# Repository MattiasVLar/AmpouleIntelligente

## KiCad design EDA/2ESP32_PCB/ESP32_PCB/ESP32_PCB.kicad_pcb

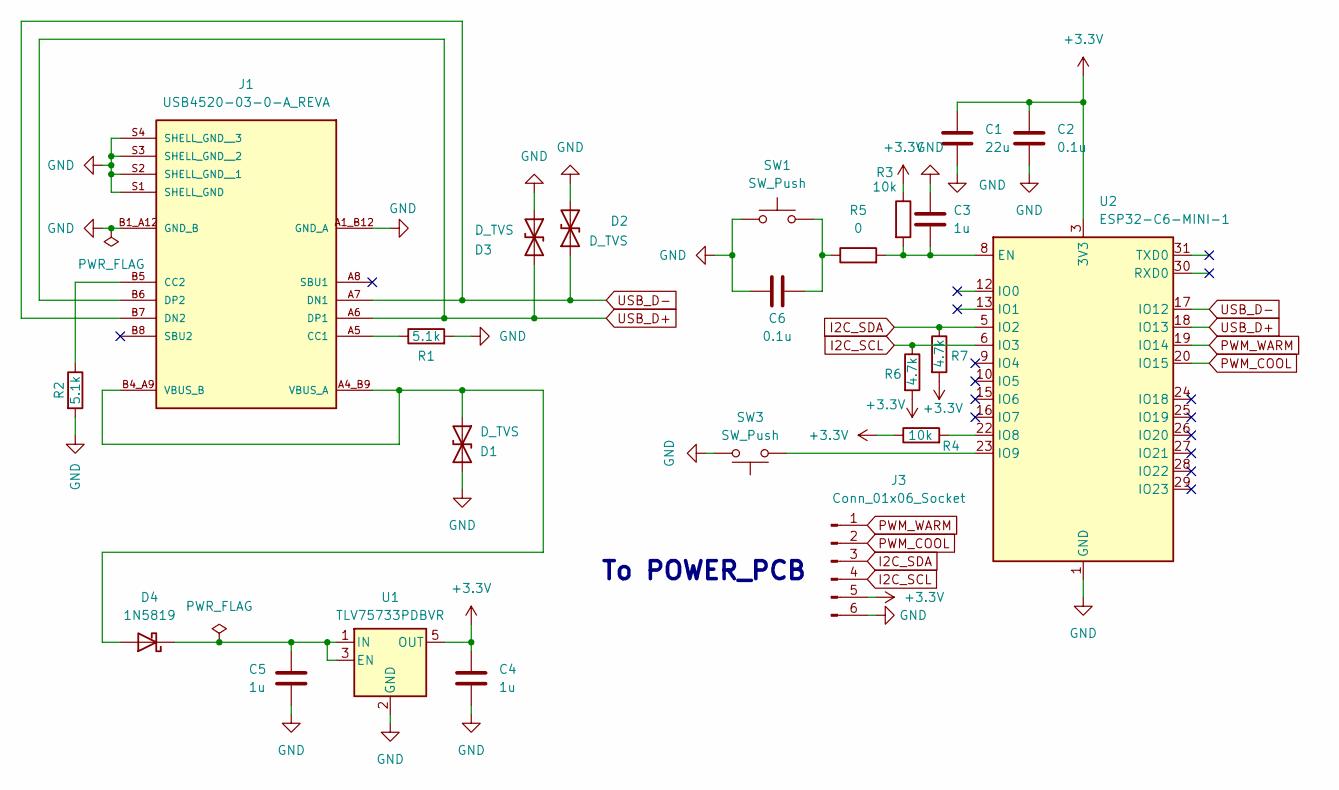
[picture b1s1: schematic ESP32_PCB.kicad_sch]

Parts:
C1: 22u; C_0603_1608Metric_Pad1.08x0.95mm_HandSolder; Digikey 1276-1274-1-ND
C2, C6: 0.1u; C_0603_1608Metric_Pad1.08x0.95mm_HandSolder; Digikey 311-1088-1-ND
C3, C4, C5: 1u; C_0603_1608Metric_Pad1.08x0.95mm_HandSolder; Digikey 445-CGA3E1X7R1C105K080DCCT-ND
D1: D_TVS; D_SOD-323F; Digikey 296-TSD05DYFRCT-ND
D2, D3: D_TVS; D_SOD-323F; Digikey 296-TSD05CDYFRCT-ND
D4: 1N5819; SDO_SOD123_DIO-L; Digikey B140HWDICT-ND
J1: USB4520-03-0-A_REVA; GCT_USB4520-03-0-A_REVA; PARTREV A
J3: Conn_01x06_Socket; EdgeConn
R1, R2: 5.1k; R_0603_1608Metric_Pad0.98x0.95mm_HandSolder; Digikey 311-5.10KHRCT-ND
R3, R4: 10k; R_0603_1608Metric_Pad0.98x0.95mm_HandSolder; Digikey 311-10.0KHRCT-ND
R5: 0; R_0603_1608Metric_Pad0.98x0.95mm_HandSolder; Digikey 311-0.0GRCT-ND
R6, R7: 4.7k; R_0603_1608Metric_Pad0.98x0.95mm_HandSolder; Digikey 311-4.70KHRCT-ND
SW1, SW3: SW_Push; SW_B3U-1000P; Digikey SW1020CT-ND
U1: TLV75733PDBVR; SOT-23-5; Digikey 296-50414-1-ND
U2: ESP32-C6-MINI-1; Digikey 1965-ESP32-C6-MINI-1-H4CT-ND

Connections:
+3.3V: C1.1, C2.2, C4.1, J3.5, R3.1, R4.1, R6.2, R7.2, U1.5 (OUT), U2.3 (3V3)
GND: C1.2, C2.1, C3.2, C4.2, C5.2, C6.2, D1.2 (A2), D2.2 (A2), D3.1 (A1), J1.A1_B12 (GND_A), J1.B1_A12 (GND_B), J1.S1 (SHELL_GND), J1.S2 (SHELL_GND__1), J1.S3 (SHELL_GND__2), J1.S4 (SHELL_GND__3), J3.6, R1.2, R2.2, SW1.1, SW3.2, U1.2 (GND), U2.1 (GND), U2.2 (GND), U2.11 (GND), U2.14 (GND), U2.36 (GND), U2.37 (GND), U2.38 (GND), U2.39 (GND), U2.40 (GND), U2.41 (GND), U2.42 (GND), U2.43 (GND), U2.44 (GND), U2.45 (GND), U2.46 (GND), U2.47 (GND), U2.48 (GND), U2.49 (GND), U2.50 (GND), U2.51 (GND), U2.52 (GND), U2.53 (GND)
I2C_SCL: J3.4, R6.1, U2.6 (IO3)
I2C_SDA: J3.3, R7.1, U2.5 (IO2)
unnamed: C6.1, R5.1, SW1.2
unnamed: D1.1 (A1), D4.2 (A), J1.A4_B9 (VBUS_A), J1.B4_A9 (VBUS_B)
unnamed: C5.1, D4.1 (K), U1.1 (IN), U1.3 (EN)
unnamed: J1.A5 (CC1), R1.1
unnamed: J1.B5 (CC2), R2.1
unnamed: C3.1, R3.2, R5.2, U2.8 (EN)
unnamed: R4.2, U2.22 (IO8)
unnamed: SW3.1, U2.23 (IO9)
PWM_COOL: J3.2, U2.20 (IO15)
PWM_WARM: J3.1, U2.19 (IO14)
USB_D+: D3.2 (A2), J1.A6 (DP1), J1.B6 (DP2), U2.18 (IO13)
USB_D-: D2.1 (A1), J1.A7 (DN1), J1.B7 (DN2), U2.17 (IO12)

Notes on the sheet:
To POWER_PCB

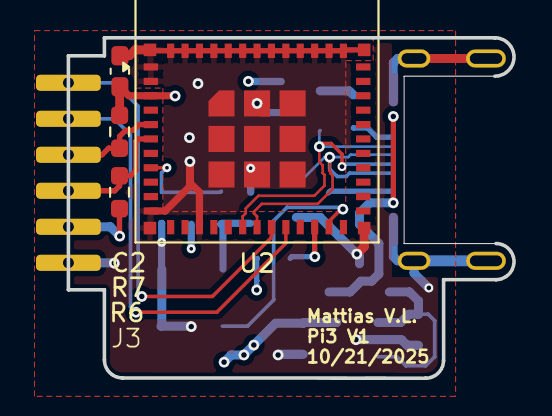
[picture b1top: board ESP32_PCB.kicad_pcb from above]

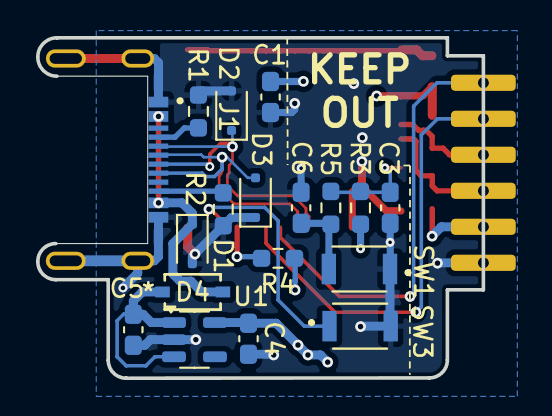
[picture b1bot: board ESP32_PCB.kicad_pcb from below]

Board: 4 copper layers, 24.8 x 18.9 mm, 23 parts (18 on the bottom side), 16 nets.

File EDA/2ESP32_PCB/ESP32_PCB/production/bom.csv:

Designator,Footprint,Quantity,Value,LCSC Part #
C1,0603,1,22u,
"C2, C6",0603,2,0.1u,
"C3, C4, C5",0603,3,1u,
"D1, D2, D3",D_SOD-323F,3,D_TVS,
D4,SDO_SOD123_DIO-L,1,1N5819,
J1,GCT_USB4520-03-0-A_REVA,1,USB4520-03-0-A_REVA,
J3,EdgeConn,1,Conn_01x06_Socket,
"R1, R2",0603,2,5.1k,
"R3, R4",0603,2,10k,
R5,0603,1,0,
"R6, R7",0603,2,4.7k,
"SW1, SW3",SW_B3U-1000P,2,SW_Push,
U1,SOT-23-5,1,TLV75533PDBV,
U2,ESP32-C6-MINI-1,1,ESP32-C6-MINI-1,

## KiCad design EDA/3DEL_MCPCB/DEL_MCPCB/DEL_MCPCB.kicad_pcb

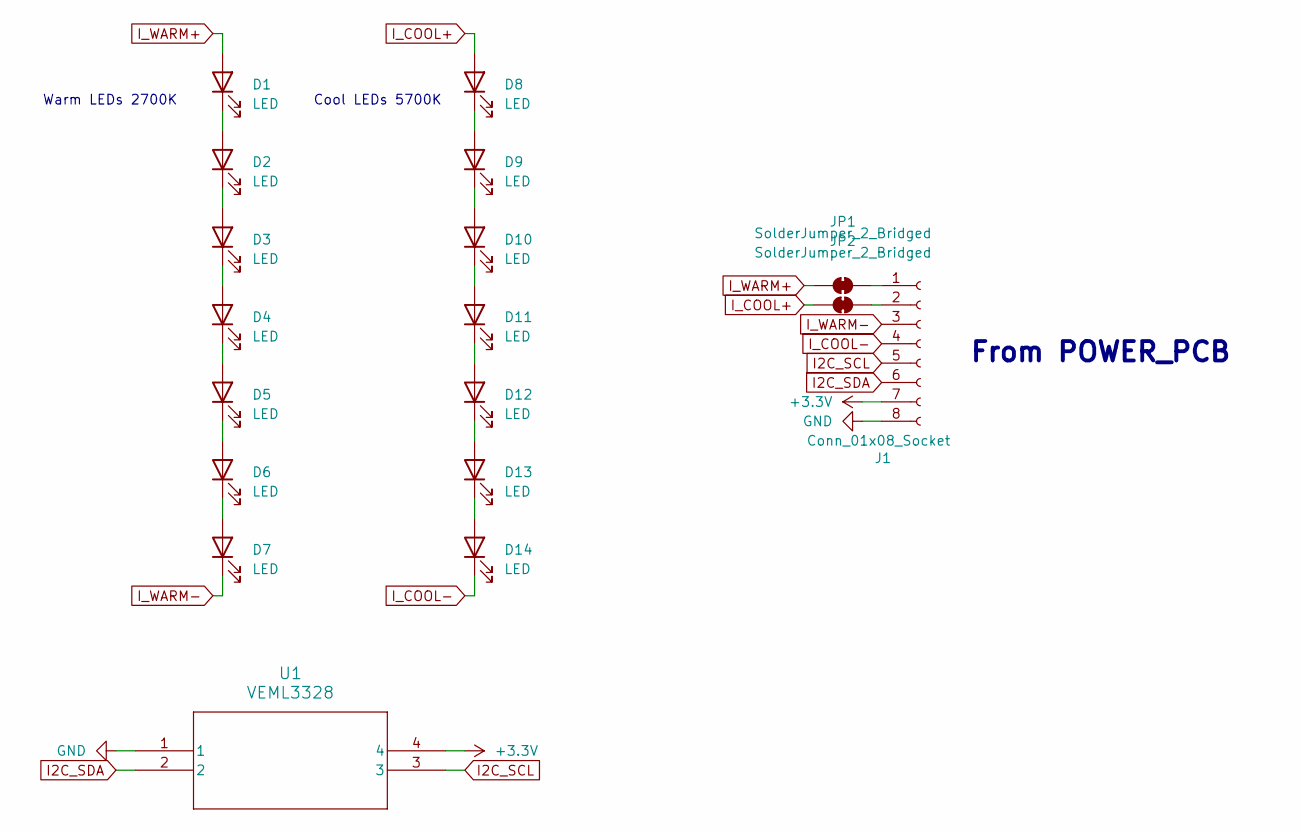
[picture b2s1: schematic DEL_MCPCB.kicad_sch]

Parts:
D1, D2, D3, D4, D5, D6, D7: LED; LED_Luminus_MP-3030-1100_3.0x3.0mm; Digikey 2138-JK3030AWT-P-U27EA0000-N0000001CT-ND
D8, D9, D10, D11, D12, D13, D14: LED; LED_Luminus_MP-3030-1100_3.0x3.0mm; Digikey 2138-JK3030AWT-P-U57EA0000-N0000001CT-ND
J1: Conn_01x08_Socket; SAMTEC_CLP-104-02-X-D; Digikey SAM1155-04-ND
JP1, JP2: SolderJumper_2_Bridged; R_1206_3216Metric_Pad1.30x1.75mm_HandSolder; Digikey RMCF1206ZT0R00CT-ND
U1: VEML3328; SMD_L3328_VIS; Digikey 751-VEML3328CT-ND

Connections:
+3.3V: J1.7, U1.4
GND: J1.8, U1.1
I2C_SCL: J1.5, U1.3
I2C_SDA: J1.6, U1.2
I_COOL+: D8.2 (A), JP2.1 (A)
I_COOL-: D14.1 (K), J1.4
I_WARM+: D1.2 (A), JP1.1 (A)
I_WARM-: D7.1 (K), J1.3
unnamed: D1.1 (K), D2.2 (A)
unnamed: D2.1 (K), D3.2 (A)
unnamed: D3.1 (K), D4.2 (A)
unnamed: D4.1 (K), D5.2 (A)
unnamed: D5.1 (K), D6.2 (A)
unnamed: D6.1 (K), D7.2 (A)
unnamed: D8.1 (K), D9.2 (A)
unnamed: D9.1 (K), D10.2 (A)
unnamed: D10.1 (K), D11.2 (A)
unnamed: D11.1 (K), D12.2 (A)
unnamed: D12.1 (K), D13.2 (A)
unnamed: D13.1 (K), D14.2 (A)
unnamed: J1.1, JP1.2 (B)
unnamed: J1.2, JP2.2 (B)

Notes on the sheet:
From POWER_PCB
Cool LEDs 5700K
Warm LEDs 2700K

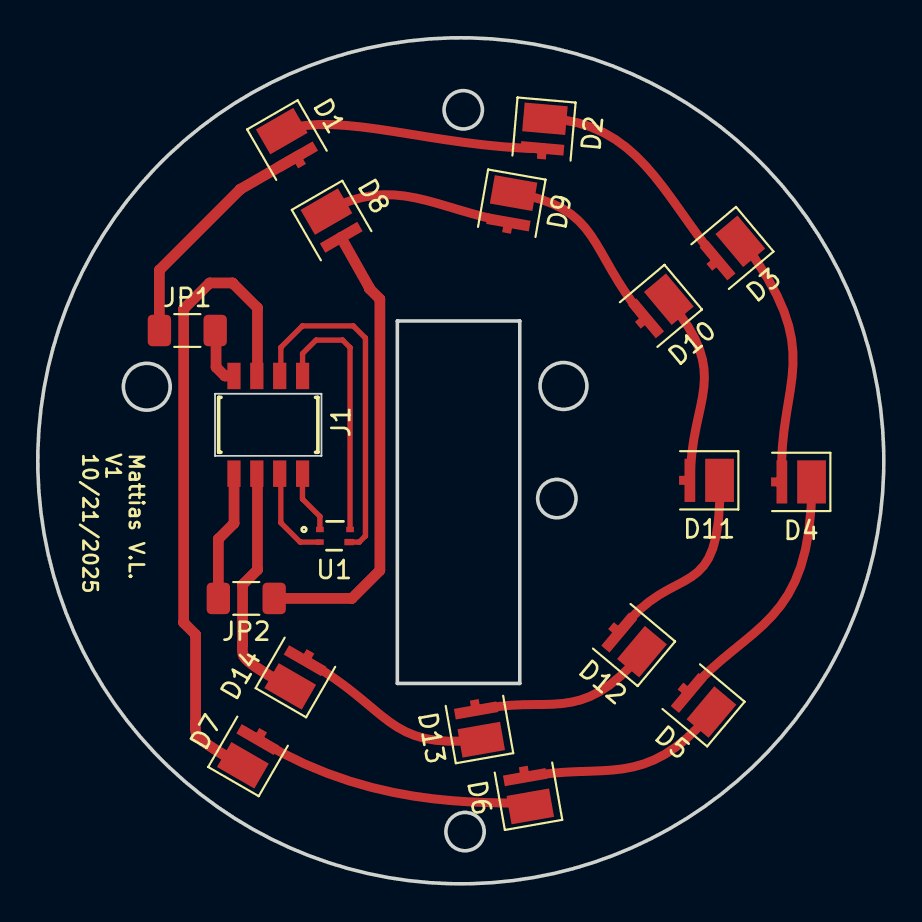
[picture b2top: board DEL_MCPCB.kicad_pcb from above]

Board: 2 copper layers, 47.0 x 47.0 mm, 18 parts (0 on the bottom side), 22 nets.

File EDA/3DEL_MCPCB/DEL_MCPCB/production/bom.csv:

Designator,Footprint,Quantity,Value,LCSC Part #
"D1, D10, D11, D12, D13, D14, D2, D3, D4, D5, D6, D7, D8, D9",LED_Luminus_MP-3030-1100_3.0x3.0mm,14,LED,
J1,SAMTEC_CLP-104-02-X-D,1,Conn_01x08_Socket,
U1,SMD_L3328_VIS,1,VEML3328,

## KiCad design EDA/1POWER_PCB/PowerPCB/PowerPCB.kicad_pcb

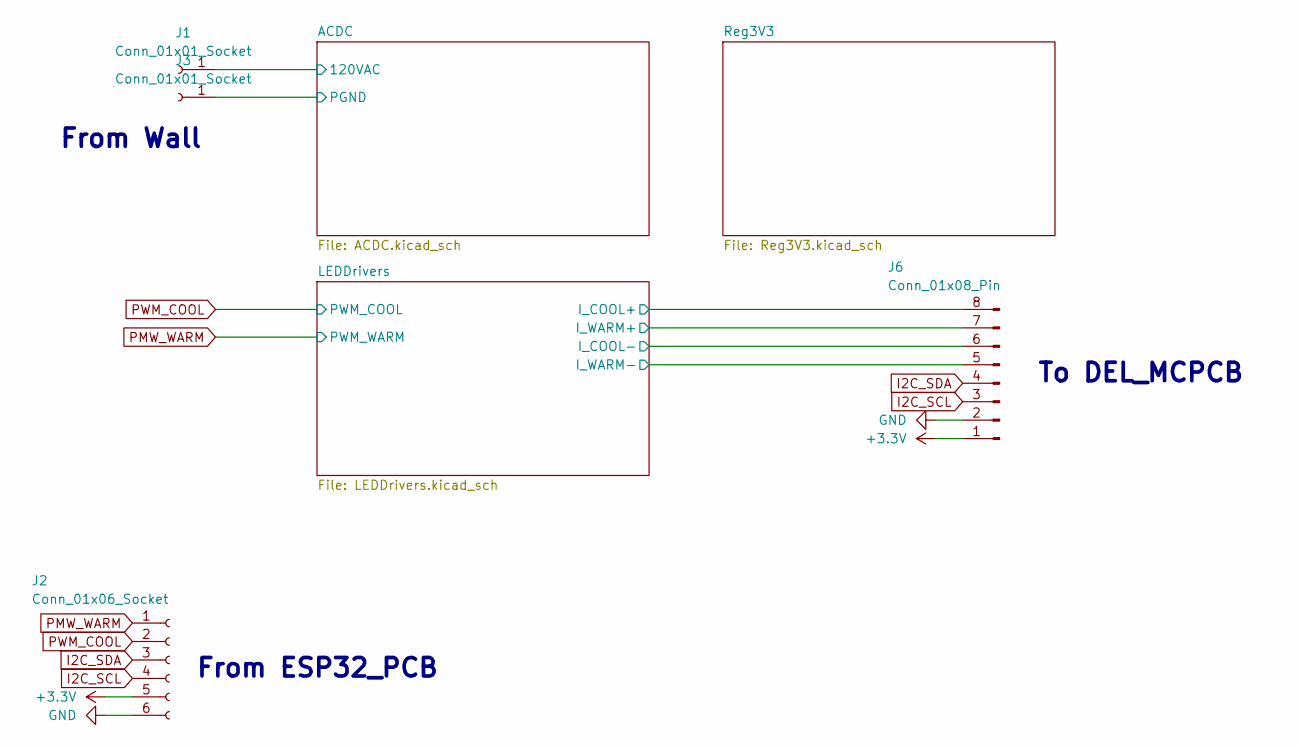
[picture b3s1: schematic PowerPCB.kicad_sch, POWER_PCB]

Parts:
J1, J3: Conn_01x01_Socket; PADPOWER
J2: Conn_01x06_Socket; EdgeConnHolePi3
J6: Conn_01x08_Pin; SAMTEC_FTSH-104-01-L-DH; Digikey SAM1160-04-ND

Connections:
+3.3V: J2.5, J6.1; also elsewhere on the board
/ACDC/120VAC: J1.1; also elsewhere on the board
/ACDC/PGND: J3.1; also elsewhere on the board
/LEDDrivers/I_COOL+: J6.8; also elsewhere on the board
/LEDDrivers/I_COOL-: J6.6; also elsewhere on the board
/LEDDrivers/I_WARM+: J6.7; also elsewhere on the board
/LEDDrivers/I_WARM-: J6.5; also elsewhere on the board
GND: J2.6, J6.2; also elsewhere on the board
I2C_SCL: J2.4, J6.3
I2C_SDA: J2.3, J6.4
PMW_WARM: J2.1; also elsewhere on the board
PWM_COOL: J2.2; also elsewhere on the board

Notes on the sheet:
From Wall
From ESP32_PCB
To DEL_MCPCB

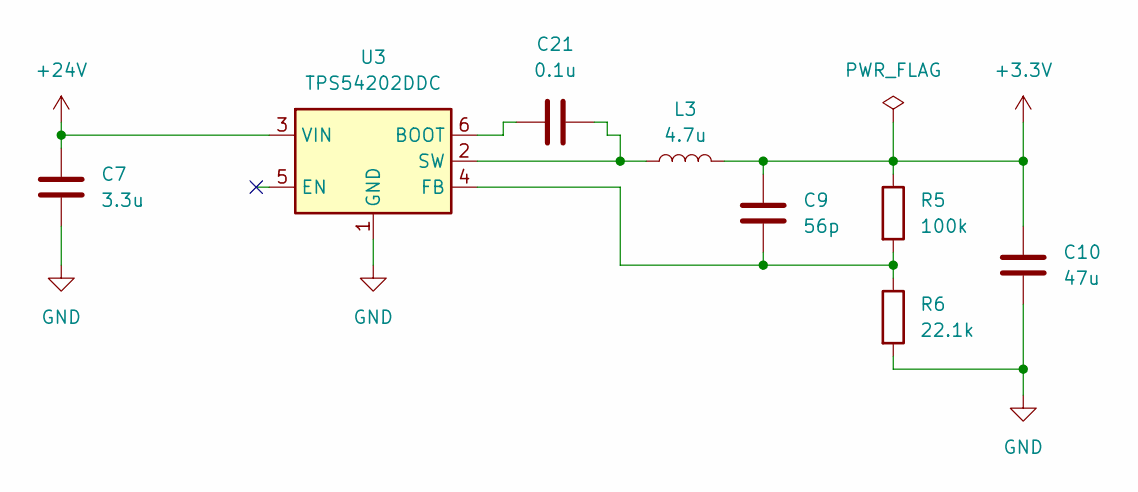
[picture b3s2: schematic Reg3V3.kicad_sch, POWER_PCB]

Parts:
C7: 3.3u; C_0805_2012Metric_Pad1.18x1.45mm_HandSolder; Digikey 445-5978-1-ND
C9: 56p; C_0805_2012Metric_Pad1.18x1.45mm_HandSolder; Digikey 311-1108-1-ND
C10: 47u; C_0805_2012Metric_Pad1.18x1.45mm_HandSolder; Digikey 587-3266-1-ND
C21: 0.1u; C_0805_2012Metric_Pad1.18x1.45mm_HandSolder; Digikey 399-C0805C104K5RACTUCT-ND
L3: 4.7u; L_Wuerth_MAPI-3020; Digikey 732-74438336047HTCT-ND
R5: 100k; R_0805_2012Metric_Pad1.20x1.40mm_HandSolder; Digikey 311-100KCRCT-ND
R6: 22.1k; R_0805_2012Metric_Pad1.20x1.40mm_HandSolder; Digikey RMCF0805FT22K1CT-ND
U3: TPS54202DDC; SOT-23-6; Digikey 296-TPS54202DDCRCT-ND

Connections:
+3.3V: C9.1, C10.2, L3.2, R5.1; also elsewhere on the board
+24V: C7.1, U3.3 (VIN); also elsewhere on the board
GND: C7.2, C10.1, R6.2, U3.1 (GND); also elsewhere on the board
unnamed: C21.1, U3.6 (BOOT)
unnamed: C9.2, R5.2, R6.1, U3.4 (FB)
unnamed: C21.2, L3.1, U3.2 (SW)

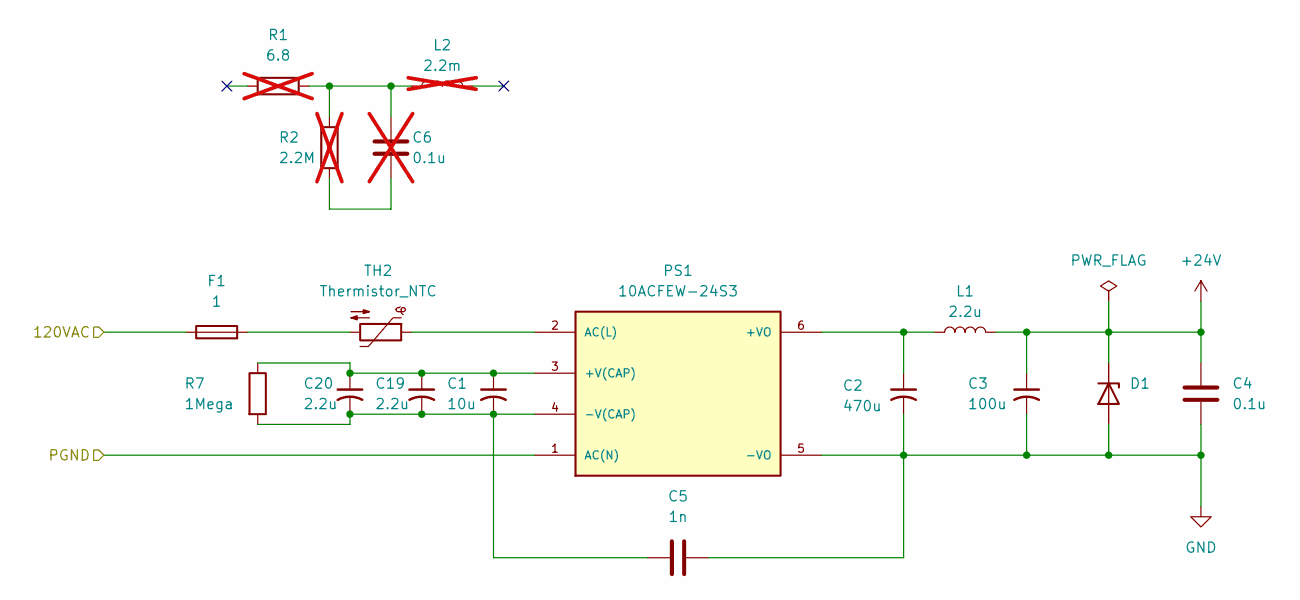
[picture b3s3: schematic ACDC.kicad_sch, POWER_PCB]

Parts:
C1: 10u; CP_Radial_D10.0mm_P5.00mm; Digikey 493-10416-1-ND
C2: 470u; CAP_UCD_8X10_NCH-L; Digikey 493-14356-1-ND
C3: 100u; CP_Radial_D6.3mm_P2.50mm; Digikey 732-9215-1-ND
C4: 0.1u; C_0805_2012Metric_Pad1.18x1.45mm_HandSolder; Digikey 399-C0805C104K5RACTUCT-ND
C5: 1n; C_Disc_D9.0mm_W5.0mm_P10.00mm; Digikey 490-DE1E3RA102MA4BH01F-ND
C6: 0.1u; R46-AC_KEM; Digikey 399-5862-ND; not fitted
C19, C20: 2.2u; CP_Radial_D6.3mm_P2.50mm; Digikey 1189-400PX2.2MEFC6.3X11-ND
D1: D_SMB; Digikey SMBJ30ALFCT-ND
F1: 1; FUSE_36911000000; Digikey F5459CT-ND
L1: 2.2u; IND_BOURNS_SRN4018; Digikey SRN4018-2R2MCT-ND
L2: 2.2m; IND_BOURNS_SRR1208; Digikey SRR1208-222KLCT-ND; not fitted
PS1: 10ACFEW-24S3; CONV_LS10-13B24R3; Digikey 3182-10ACFEW_24S3-ND
R1: 6.8; RES_NKN3WS_15P5X5_YAG; Digikey 13-NKN3WSJR-73-6R8CT-ND; not fitted
R2: 2.2M; Digikey MFR-25FBF52-2M2-ND; not fitted
R7: 1Mega; R_2010_5025Metric_Pad1.40x2.65mm_HandSolder; Digikey 2019-HV732HTTE1004FCT-ND
TH2: Thermistor_NTC; R_Axial_DIN0207_L6.3mm_D2.5mm_P5.08mm_Vertical; Digikey 317-1158-ND

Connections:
+24V: C3.1, C4.1, D1.1 (K), L1.2; also elsewhere on the board
/ACDC/120VAC: F1.1; also elsewhere on the board
/ACDC/PGND: PS1.1 (AC(N)); also elsewhere on the board
GND: C2.2, C3.2, C4.2, C5.2, D1.2 (A), PS1.5 (-VO); also elsewhere on the board
unnamed: C6.1, R2.2
unnamed: C6.2, L2.1, R1.1, R2.1
unnamed: F1.2, TH2.2
unnamed: C1.1, C19.1, C20.1, PS1.3 (+V(CAP)), R7.1
unnamed: C2.1, L1.1, PS1.6 (+VO)
unnamed: C1.2, C5.1, C19.2, C20.2, PS1.4 (-V(CAP)), R7.2
unnamed: PS1.2 (AC(L)), TH2.1

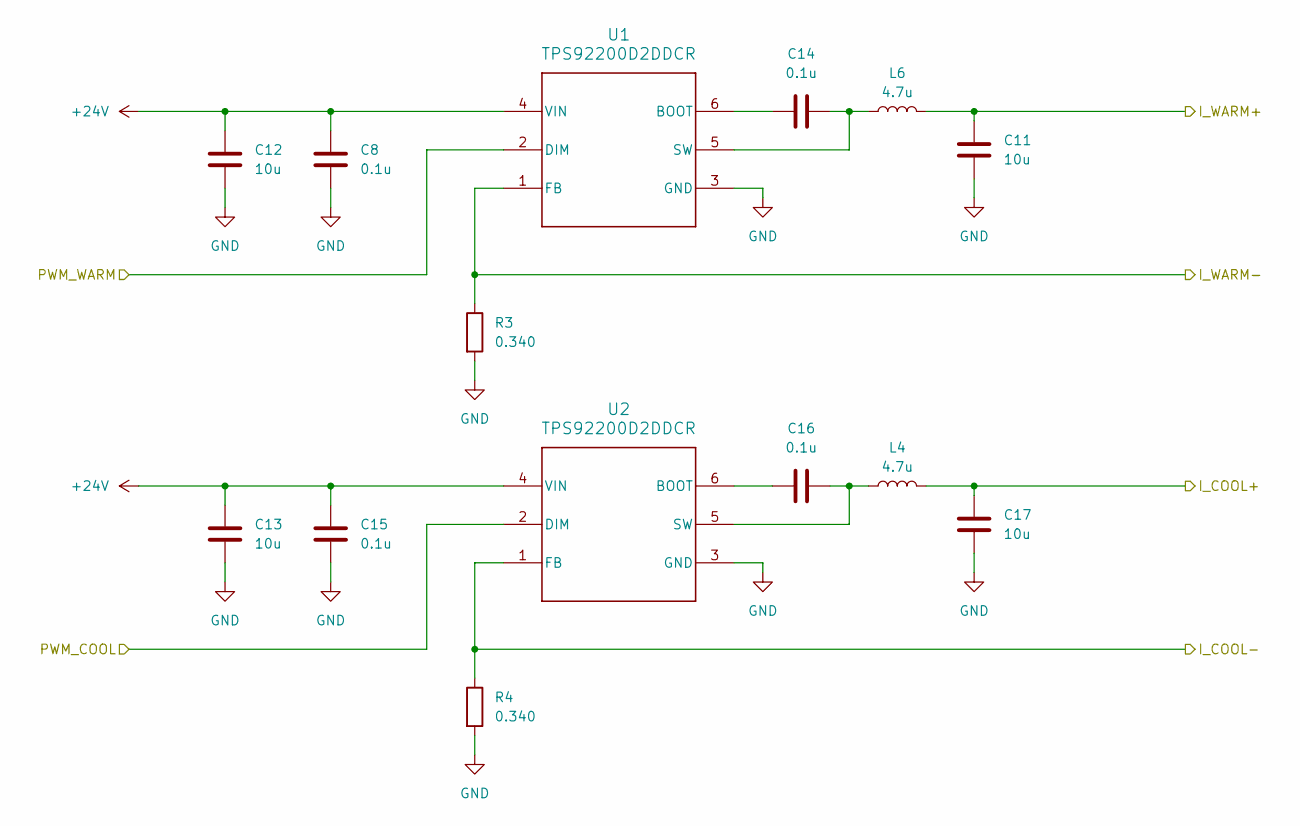
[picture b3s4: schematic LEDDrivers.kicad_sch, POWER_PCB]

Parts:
C8, C14, C15, C16: 0.1u; C_0805_2012Metric_Pad1.18x1.45mm_HandSolder; Digikey 399-C0805C104K5RACTUCT-ND
C11, C12, C13, C17: 10u; C_0805_2012Metric_Pad1.18x1.45mm_HandSolder; Digikey 490-18663-1-ND
L4, L6: 4.7u; IND_MAMK2520T1R0M_TAY-L; Digikey 587-3228-1-ND
R3, R4: 0.340; R_0805_2012Metric_Pad1.20x1.40mm_HandSolder; Digikey 1712-RLC73K2AR34FTDCT-ND
U1, U2: TPS92200D2DDCR; DDC0006A_L; Digikey 296-TPS92200D2DDCRCT-ND

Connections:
+24V: C8.2, C12.1, C13.1, C15.2, U1.4 (VIN), U2.4 (VIN); also elsewhere on the board
/LEDDrivers/I_COOL+: C17.1, L4.2; also elsewhere on the board
/LEDDrivers/I_COOL-: R4.1, U2.1 (FB); also elsewhere on the board
/LEDDrivers/I_WARM+: C11.1, L6.2; also elsewhere on the board
/LEDDrivers/I_WARM-: R3.1, U1.1 (FB); also elsewhere on the board
GND: C8.1, C11.2, C12.2, C13.2, C15.1, C17.2, R3.2, R4.2, U1.3 (GND), U2.3 (GND); also elsewhere on the board
unnamed: C14.2, U1.6 (BOOT)
unnamed: C14.1, L6.1, U1.5 (SW)
unnamed: C16.2, U2.6 (BOOT)
unnamed: C16.1, L4.1, U2.5 (SW)
PMW_WARM: U1.2 (DIM); also elsewhere on the board
PWM_COOL: U2.2 (DIM); also elsewhere on the board

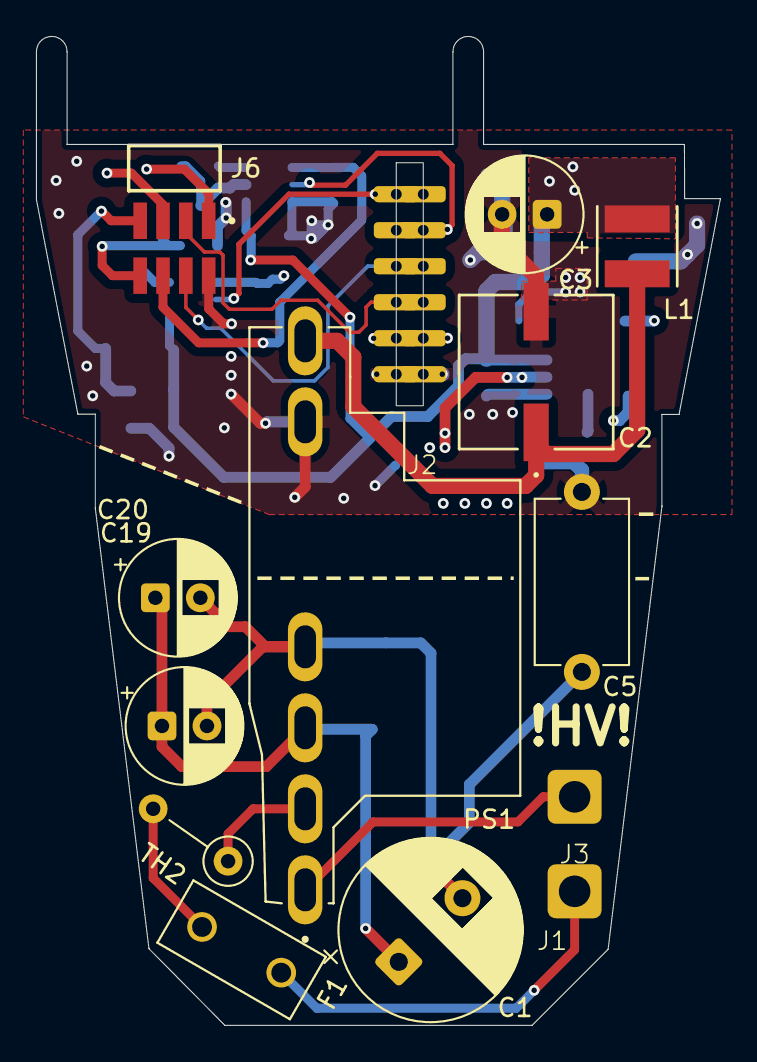
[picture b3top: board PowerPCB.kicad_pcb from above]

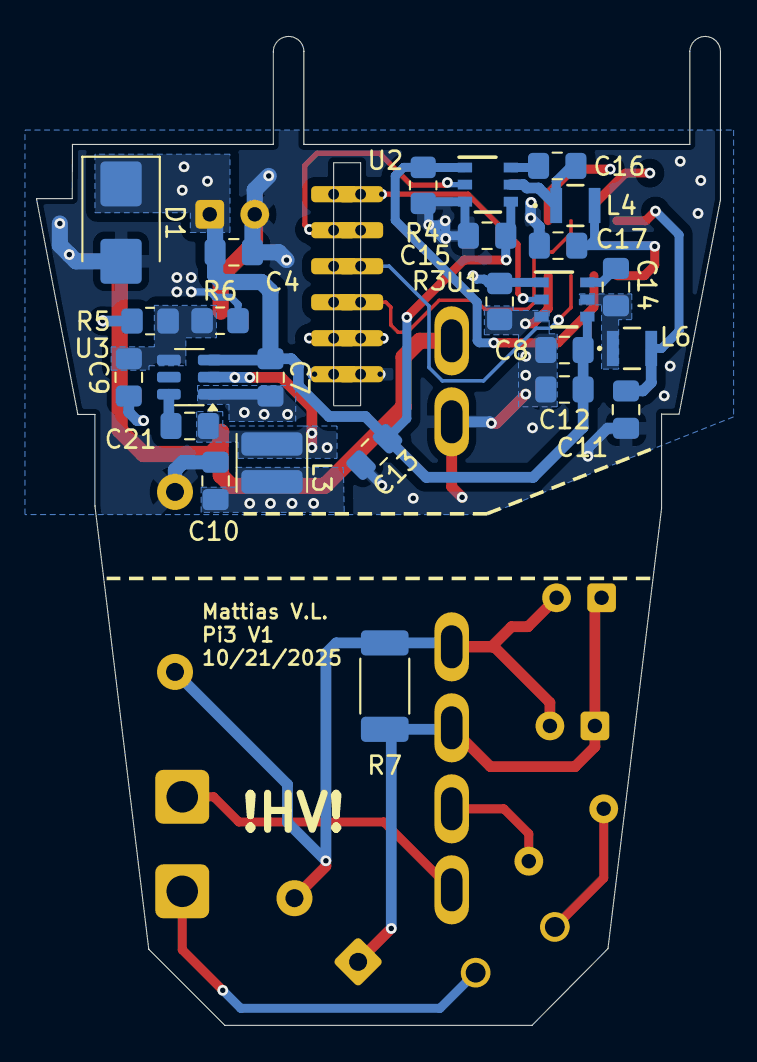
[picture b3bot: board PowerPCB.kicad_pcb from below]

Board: 4 copper layers, 38.0 x 54.9 mm, 39 parts (25 on the bottom side), 25 nets.

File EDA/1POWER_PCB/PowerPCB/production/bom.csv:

Designator,Footprint,Quantity,Value,LCSC Part #
C1,CP_Radial_D10.0mm_P5.00mm,1,10u,
C10,0805,1,47u,
"C11, C12, C13, C17",0805,4,10u,
"C14, C15, C16, C21, C4, C8",0805,6,0.1u,
"C19, C20",CP_Radial_D6.3mm_P2.50mm,2,2.2u,
C2,CAP_UCD_8X10_NCH-L,1,470u,
C3,CP_Radial_D6.3mm_P2.50mm,1,100u,
C5,C_Disc_D9.0mm_W5.0mm_P10.00mm,1,1n,
C7,0805,1,3.3u,
C9,0805,1,56p,
D1,D_SMB,1,~,
F1,FUSE_36911000000,1,1,
"J1, J3",PADPOWER,2,Conn_01x01_Socket,
J2,EdgeConnHolePi3,1,Conn_01x06_Socket,
J6,SAMTEC_FTSH-104-01-L-DH,1,Conn_01x08_Pin,
L1,IND_BOURNS_SRN4018,1,2.2u,
L3,L_Wuerth_MAPI-3020,1,L,
"L4, L6",IND_MAMK2520T1R0M_TAY-L,2,4.7u,
PS1,CONV_LS10-13B24R3,1,10ACFEW-24S3,
"R3, R4",0805,2,0.340,
R5,0805,1,100k,
R6,0805,1,22.1k,
R7,2010,1,1Mega,
TH2,R_Axial_DIN0207_L6.3mm_D2.5mm_P5.08mm_Vertical,1,Thermistor_NTC,
"U1, U2",DDC0006A_L,2,TPS92200D2DDCR,
U3,SOT-23-6,1,TPS54202DDC,

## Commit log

2025-12-03 Fix project name formatting in README
2025-12-03 Init
2025-12-03 CodeFolder
2025-12-03 CleanUp EDA
2025-12-05 Je sais plus
2025-12-05 Ajout Affiche
2025-12-05 Add image to README for visual representation
2025-12-05 Add BSD 3-Clause License file
    This file contains the BSD 3-Clause License text, outlining the terms for redistribution and use of the software.
2025-12-05 Update LICENSE
2025-12-05 Rename LICENSE to CODE/LICENSE
2025-12-05 Add BSD 3-Clause License to the project
2025-12-07 Changement de commentaires dans CODE
